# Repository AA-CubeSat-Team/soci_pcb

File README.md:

# soci_pcb

## design_rules
Directory for the design rules of various PCB manufacturers.

## libraries
Directory for Eagle part/component libraries used across PCB designs.

## projects
Repository for PCBs designed for soci in EAGLE

Make sure to update your libraries, design rules, and projects paths by going to Options -> Directories in EAGLE.

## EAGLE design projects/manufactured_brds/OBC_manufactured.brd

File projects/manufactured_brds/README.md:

## This folder Contains all of the Eagle files for boards that have been previously manufactured

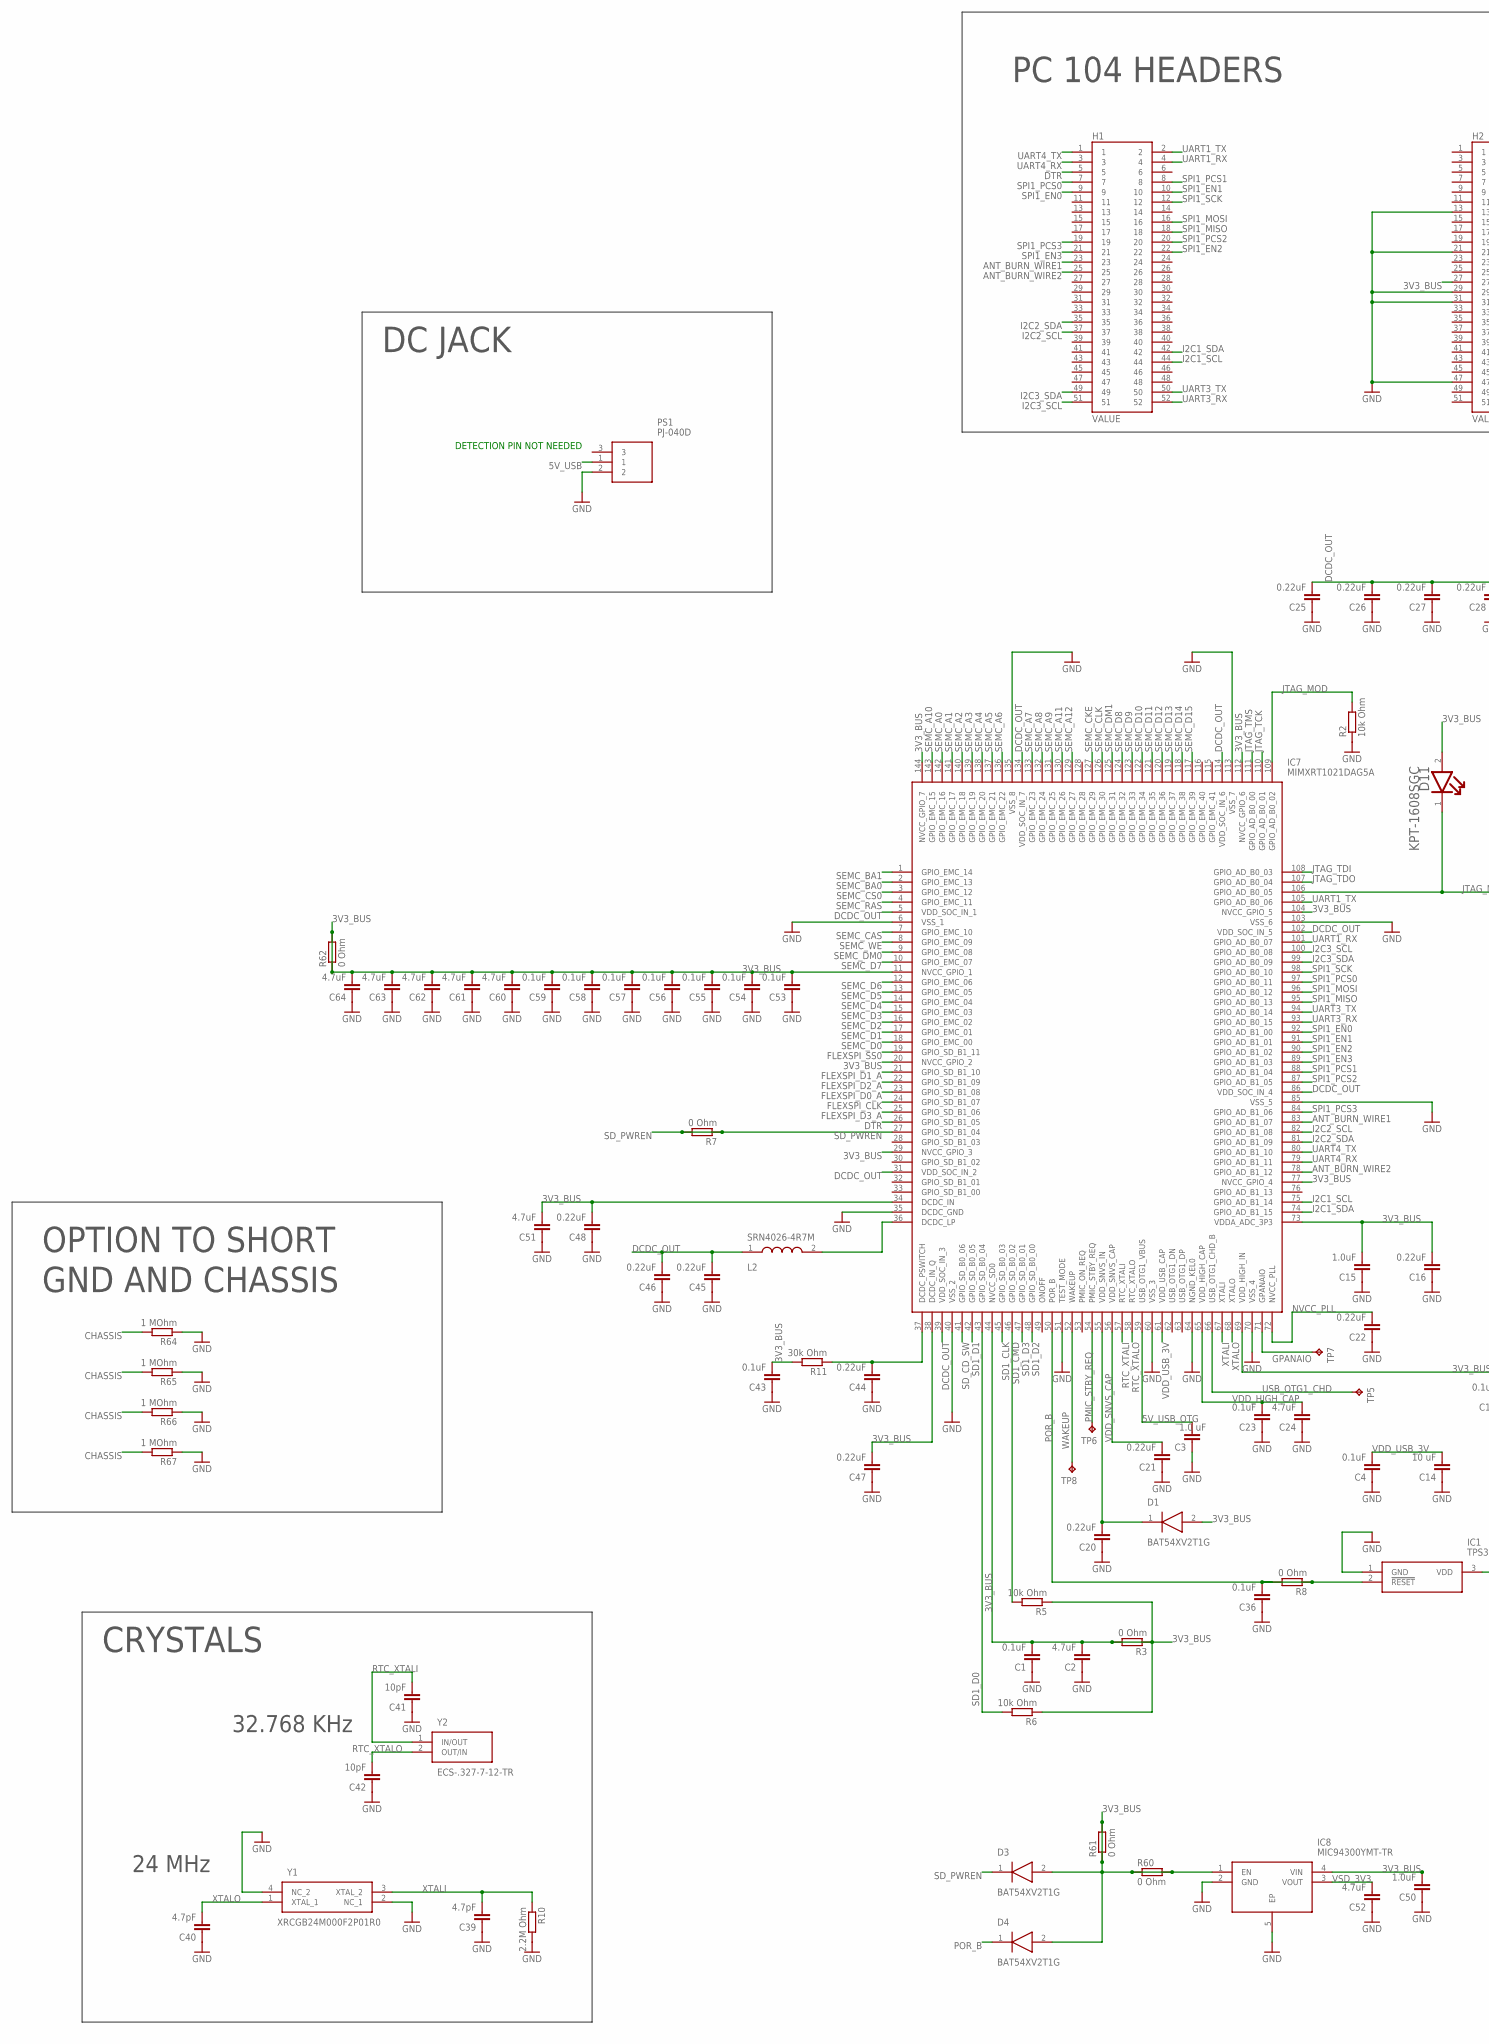
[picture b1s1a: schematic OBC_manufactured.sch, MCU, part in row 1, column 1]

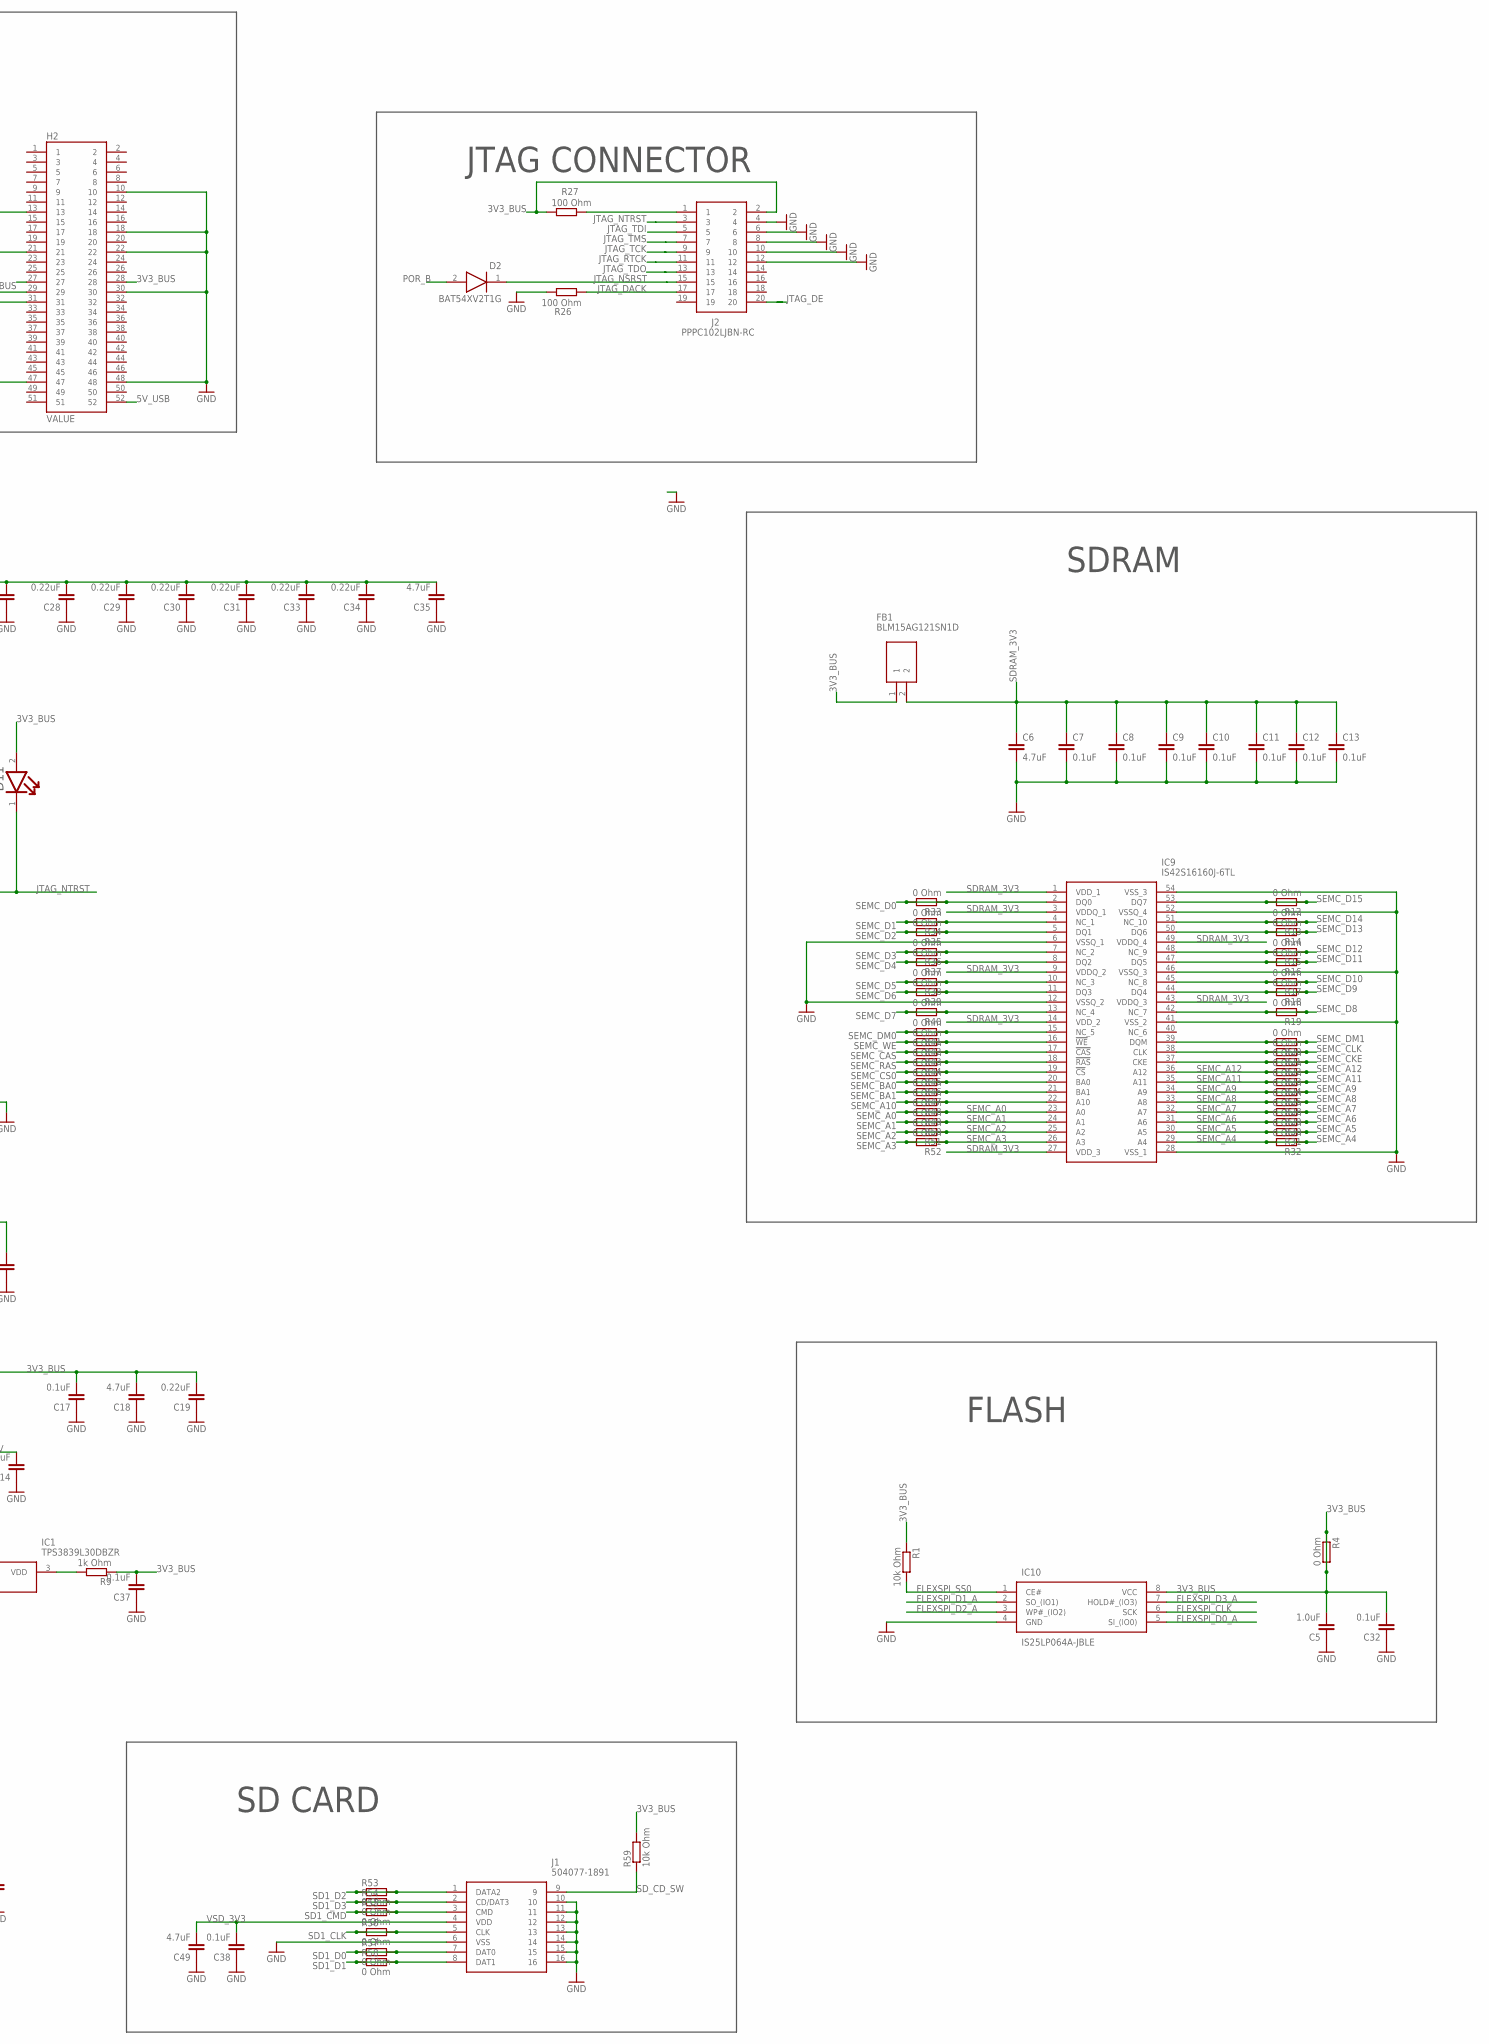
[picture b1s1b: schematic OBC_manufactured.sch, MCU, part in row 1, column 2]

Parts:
C1, C4, C7, C8, C9, C10, C11, C12, C13, C17, C23, C32, C36, C37, C38, C43, C53, C54, C55, C56, C57, C58, C59: 0.1uF; C0402K
C2, C6, C18, C24, C35, C49, C51, C52, C60, C61, C62, C63, C64: 4.7uF; C0402K
C3: 1.0 uF; C0402K
C5, C15, C50: 1.0uF; C0402K
C14: 10 uF; C0402K
C16, C19, C20, C21, C22, C25, C26, C27, C28, C29, C30, C31, C33, C34, C44, C45, C46, C47, C48: 0.22uF; C0402K
C39, C40: 4.7pF; C0402K
C41, C42: 10pF; C0402K
D1, D2, D3, D4: BAT54XV2T1G; SODFL1608X70N
D11: KINGBRIGHT_KPT-1608SGCKINGBRIGHT_KPT-1608SGC_0_0; KINGBRIGHT_KPT-1608SGC_0
FB1: BLM15AG121SN1D; NFZ15SG152SN10B
H1, H2: ESQ-126-39-G-D; SAMTEC_ESQ-126-39-G-D
IC1: TPS3839L30DBZR; SOT95P237X112-3N
IC7: MIMXRT1021DAG5A; QFP50P2200X2200X160-144N
IC8: MIC94300YMT-TR; SON50P160X120X60-5N
IC9: IS42S16160J-6TL; SOP80P1176X120-54N
IC10: IS25LP064A-JBLE; SOIC127P790X216-8N
J1: 504077-1891; 5040771891
J2: PPPC102LJBN-RC; RHDRRA20W60P254X254_2X10_2590X
L2: SRN4026-4R7M; SRN4026
PS1: PJ-040D; PJ040D
R1, R2, R5, R6, R59: 10k Ohm; R0402
R3, R4, R7, R8, R12, R13, R14, R15, R16, R17, R18, R19, R20, R21, R22, R23, R24, R25, R28, R29, R30, R31, R32, R33, R34, R35, R36, R37, R38, R39, R40, R41, R42, R43, R44, R45, R46, R47, R48, R49, R50, R51, R52, R53, R54, R55, R56, R57, R58, R60, R61, R62: 0 Ohm; R0402
R9: 1k Ohm; R0402
R10: 2.2M Ohm; R0402
R11: 30k Ohm; R0402
R26, R27: 100 Ohm; R0402
R64, R65, R66, R67: 1 MOhm; R0805
TP5, TP6, TP7, TP8: TPTP06R; TP06R
Y1: XRCGB24M000F2P01R0
Y2: ECS-.327-7-12-TR; ECS327712TR

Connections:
3V3_BUS: C1.2, C2.2, C5.2, C15.2, C16.2, C17.2, C18.2, C19.2, C32.2, C37.2, C43.2, C47.2, C48.2, C50.2, C51.2, C53.2, C54.2, C55.2, C56.2, C57.2, C58.2, C59.2, C60.2, C61.2, C62.2, C63.2, C64.2, D1.2 (A), D3.2 (A), D4.2 (A), D11.2 (ANODE), FB1.1, H2.27, H2.28, IC7.11 (NVCC_GPIO_1), IC7.20 (NVCC_GPIO_2), IC7.29 (NVCC_GPIO_3), IC7.34 (DCDC_IN), IC7.38 (DCDC_IN_Q), IC7.44 (NVCC_SD0), IC7.69 (VDD_HIGH_IN), IC7.73 (VDDA_ADC_3P3), IC7.77 (NVCC_GPIO_4), IC7.104 (NVCC_GPIO_5), IC7.112 (NVCC_GPIO_6), IC7.144 (NVCC_GPIO_7), IC8.1 (EN), IC8.4 (VIN), IC10.8 (VCC), J2.2, R1.1, R3.1, R3.2, R4.1, R4.2, R5.1, R6.1, R9.1, R11.2, R27.1, R59.2, R60.1, R60.2, R61.1, R61.2, R62.1, R62.2
5V_USB: H2.52, PS1.1
5V_USB_OTG: C3.2, IC7.59 (USB_OTG1_VBUS)
ANT_BURN_WIRE1: H1.23, IC7.83 (GPIO_AD_B1_07)
ANT_BURN_WIRE2: H1.25, IC7.78 (GPIO_AD_B1_12)
CHASSIS: R64.2, R65.2, R66.2, R67.2
DCDC_OUT: C25.2, C26.2, C27.2, C28.2, C29.2, C30.2, C31.2, C33.2, C34.2, C35.2, C45.2, C46.2, IC7.5 (VDD_SOC_IN_1), IC7.31 (VDD_SOC_IN_2), IC7.39 (VDD_SOC_IN_3), IC7.86 (VDD_SOC_IN_4), IC7.102 (VDD_SOC_IN_5), IC7.114 (VDD_SOC_IN_6), IC7.134 (VDD_SOC_IN_7), L2.1
DTR: H1.5, IC7.26 (GPIO_SD_B1_05)
FLEXSPI_CLK: IC7.24 (GPIO_SD_B1_07), IC10.6 (SCK)
FLEXSPI_D0_A: IC7.23 (GPIO_SD_B1_08), IC10.5 (SI_(IO0))
FLEXSPI_D1_A: IC7.21 (GPIO_SD_B1_10), IC10.2 (SO_(IO1))
FLEXSPI_D2_A: IC7.22 (GPIO_SD_B1_09), IC10.3 (WP#_(IO2))
FLEXSPI_D3_A: IC7.25 (GPIO_SD_B1_06), IC10.7 (HOLD#_(IO3))
FLEXSPI_SS0: IC7.19 (GPIO_SD_B1_11), IC10.1 (CE#), R1.2
GND: C1.1, C2.1, C3.1, C4.1, C5.1, C6.2, C7.2, C8.2, C9.2, C10.2, C11.2, C12.2, C13.2, C14.1, C15.1, C16.1, C17.1, C18.1, C19.1, C20.1, C21.1, C22.1, C23.1, C24.1, C25.1, C26.1, C27.1, C28.1, C29.1, C30.1, C31.1, C32.1, C33.1, C34.1, C35.1, C36.1, C37.1, C38.1, C39.1, C40.1, C41.1, C42.1, C43.1, C44.1, C45.1, C46.1, C47.1, C48.1, C49.1, C50.1, C51.1, C52.1, C53.1, C54.1, C55.1, C56.1, C57.1, C58.1, C59.1, C60.1, C61.1, C62.1, C63.1, C64.1, H2.10, H2.13, H2.18, H2.21, H2.22, H2.29, H2.30, H2.31, H2.47, H2.48, IC1.1 (GND), IC7.6 (VSS_1), IC7.35 (DCDC_GND), IC7.40 (VSS_2), IC7.51 (TEST_MODE), IC7.60 (VSS_3), IC7.64 (NGND_KEL0), IC7.70 (VSS_4), IC7.85 (VSS_5), IC7.103 (VSS_6), IC7.113 (VSS_7), IC7.135 (VSS_8), IC8.2 (GND), IC8.5 (EP), IC9.6 (VSSQ_1), IC9.12 (VSSQ_2), IC9.28 (VSS_1), IC9.41 (VSS_2), IC9.46 (VSSQ_3), IC9.52 (VSSQ_4), IC9.54 (VSS_3), IC10.4 (GND), J1.6 (VSS), J1.10, J1.11, J1.12, J1.13, J1.14, J1.15, J1.16, J2.4, J2.6, J2.8, J2.10, J2.12, PS1.2, R2.1, R10.2, R26.2, R64.1, R65.1, R66.1, R67.1, Y1.2 (NC_1), Y1.4 (NC_2)
GPANAIO: IC7.71 (GPANAIO), TP7.TP
I2C1_SCL: H1.44, IC7.75 (GPIO_AD_B1_14)
I2C1_SDA: H1.42, IC7.74 (GPIO_AD_B1_15)
I2C2_SCL: H1.37, IC7.82 (GPIO_AD_B1_08)
I2C2_SDA: H1.35, IC7.81 (GPIO_AD_B1_09)
I2C3_SCL: H1.51, IC7.100 (GPIO_AD_B0_08)
I2C3_SDA: H1.49, IC7.99 (GPIO_AD_B0_09)
JTAG_DACK: J2.17, R26.1
JTAG_DE: J2.20
JTAG_MOD: IC7.109 (GPIO_AD_B0_02), R2.2
JTAG_NSRST: D2.1 (K), J2.15
JTAG_NTRST: D11.1 (CATHODE), IC7.106 (GPIO_AD_B0_05), J2.3
JTAG_RTCK: J2.11
JTAG_TCK: IC7.110 (GPIO_AD_B0_01), J2.9
JTAG_TDI: IC7.108 (GPIO_AD_B0_03), J2.5
JTAG_TDO: IC7.107 (GPIO_AD_B0_04), J2.13
JTAG_TMS: IC7.111 (GPIO_AD_B0_00), J2.7
unnamed: J2.1, R27.2
unnamed: IC1.3 (VDD), R9.2
unnamed: IC7.36 (DCDC_LP), L2.2
unnamed: C44.2, IC7.37 (DCDC_PSWITCH), R11.1
unnamed: C20.2, D1.1 (K), IC7.55 (VDD_SNVS_IN)
NVCC_PLL: C22.2, IC7.72 (NVCC_PLL)
PMIC_STBY_REQ: IC7.54 (PMIC_STBY_REQ), TP6.TP
POR_B: C36.2, D2.2 (A), D4.1 (K), IC1.2 (!RESET), IC7.50 (POR_B), R8.1, R8.2
RTC_XTALI: C41.2, IC7.57 (RTC_XTALI), Y2.1 (IN/OUT)
RTC_XTALO: C42.2, IC7.58 (RTC_XTALO), Y2.2 (OUT/IN)
SD1_CLK: IC7.45 (GPIO_SD_B0_03), J1.5 (CLK), R56.1, R56.2
SD1_CMD: IC7.46 (GPIO_SD_B0_02), J1.3 (CMD), R5.2, R55.1, R55.2
SD1_D0: IC7.43 (GPIO_SD_B0_04), J1.7 (DAT0), R6.2, R57.1, R57.2
SD1_D1: IC7.42 (GPIO_SD_B0_05), J1.8 (DAT1), R58.1, R58.2
SD1_D2: IC7.48 (GPIO_SD_B0_00), J1.1 (DATA2), R53.1, R53.2
SD1_D3: IC7.47 (GPIO_SD_B0_01), J1.2 (CD/DAT3), R54.1, R54.2
SDRAM_3V3: C6.1, C7.1, C8.1, C9.1, C10.1, C11.1, C12.1, C13.1, FB1.2, IC9.1 (VDD_1), IC9.3 (VDDQ_1), IC9.9 (VDDQ_2), IC9.14 (VDD_2), IC9.27 (VDD_3), IC9.43 (VDDQ_3), IC9.49 (VDDQ_4)
SD_CD_SW: IC7.41 (GPIO_SD_B0_06), J1.9, R59.1
SD_PWREN: D3.1 (K), IC7.27 (GPIO_SD_B1_04), R7.1, R7.2
SEMC_A0: IC7.142 (GPIO_EMC_16), IC9.23 (A0), R49.1, R49.2
SEMC_A1: IC7.141 (GPIO_EMC_17), IC9.24 (A1), R50.1, R50.2
SEMC_A2: IC7.140 (GPIO_EMC_18), IC9.25 (A2), R51.1, R51.2
SEMC_A3: IC7.139 (GPIO_EMC_19), IC9.26 (A3), R52.1, R52.2
SEMC_A4: IC7.138 (GPIO_EMC_20), IC9.29 (A4), R32.1, R32.2
SEMC_A5: IC7.137 (GPIO_EMC_21), IC9.30 (A5), R31.1, R31.2
SEMC_A6: IC7.136 (GPIO_EMC_22), IC9.31 (A6), R30.1, R30.2
SEMC_A7: IC7.133 (GPIO_EMC_23), IC9.32 (A7), R29.1, R29.2
SEMC_A8: IC7.132 (GPIO_EMC_24), IC9.33 (A8), R28.1, R28.2
SEMC_A9: IC7.131 (GPIO_EMC_25), IC9.34 (A9), R25.1, R25.2
SEMC_A10: IC7.143 (GPIO_EMC_15), IC9.22 (A10), R48.1, R48.2
SEMC_A11: IC7.130 (GPIO_EMC_26), IC9.35 (A11), R24.1, R24.2
SEMC_A12: IC7.129 (GPIO_EMC_27), IC9.36 (A12), R23.1, R23.2
SEMC_BA0: IC7.2 (GPIO_EMC_13), IC9.20 (BA0), R46.1, R46.2
SEMC_BA1: IC7.1 (GPIO_EMC_14), IC9.21 (BA1), R47.1, R47.2
SEMC_CAS: IC7.7 (GPIO_EMC_10), IC9.17 (!CAS), R43.1, R43.2
SEMC_CKE: IC7.127 (GPIO_EMC_29), IC9.37 (CKE), R22.1, R22.2
SEMC_CLK: IC7.126 (GPIO_EMC_30), IC9.38 (CLK), R21.1, R21.2
SEMC_CS0: IC7.3 (GPIO_EMC_12), IC9.19 (!CS), R45.1, R45.2
SEMC_D0: IC7.18 (GPIO_EMC_00), IC9.2 (DQ0), R33.1, R33.2
SEMC_D1: IC7.17 (GPIO_EMC_01), IC9.4 (NC_1), R34.1, R34.2
SEMC_D2: IC7.16 (GPIO_EMC_02), IC9.5 (DQ1), R35.1, R35.2
SEMC_D3: IC7.15 (GPIO_EMC_03), IC9.7 (NC_2), R36.1, R36.2
SEMC_D4: IC7.14 (GPIO_EMC_04), IC9.8 (DQ2), R37.1, R37.2
SEMC_D5: IC7.13 (GPIO_EMC_05), IC9.10 (NC_3), R38.1, R38.2
SEMC_D6: IC7.12 (GPIO_EMC_06), IC9.11 (DQ3), R39.1, R39.2
SEMC_D7: IC7.10 (GPIO_EMC_07), IC9.13 (NC_4), R40.1, R40.2
SEMC_D8: IC7.124 (GPIO_EMC_32), IC9.42 (NC_7), R19.1, R19.2
SEMC_D9: IC7.123 (GPIO_EMC_33), IC9.44 (DQ4), R18.1, R18.2
SEMC_D10: IC7.122 (GPIO_EMC_34), IC9.45 (NC_8), R17.1, R17.2
SEMC_D11: IC7.121 (GPIO_EMC_35), IC9.47 (DQ5), R16.1, R16.2
SEMC_D12: IC7.120 (GPIO_EMC_36), IC9.48 (NC_9), R15.1, R15.2
SEMC_D13: IC7.119 (GPIO_EMC_37), IC9.50 (DQ6), R14.1, R14.2
SEMC_D14: IC7.118 (GPIO_EMC_38), IC9.51 (NC_10), R13.1, R13.2
SEMC_D15: IC7.117 (GPIO_EMC_39), IC9.53 (DQ7), R12.1, R12.2
SEMC_DM0: IC7.9 (GPIO_EMC_08), IC9.15 (NC_5), R41.1, R41.2
SEMC_DM1: IC7.125 (GPIO_EMC_31), IC9.39 (DQM), R20.1, R20.2
SEMC_RAS: IC7.4 (GPIO_EMC_11), IC9.18 (!RAS), R44.1, R44.2
SEMC_WE: IC7.8 (GPIO_EMC_09), IC9.16 (!WE), R42.1, R42.2
SPI1_EN0: H1.9, IC7.92 (GPIO_AD_B1_00)
SPI1_EN1: H1.10, IC7.91 (GPIO_AD_B1_01)
SPI1_EN2: H1.22, IC7.90 (GPIO_AD_B1_02)
SPI1_EN3: H1.21, IC7.89 (GPIO_AD_B1_03)
SPI1_MISO: H1.18, IC7.95 (GPIO_AD_B0_13)
SPI1_MOSI: H1.16, IC7.96 (GPIO_AD_B0_12)
SPI1_PCS0: H1.7, IC7.97 (GPIO_AD_B0_11)
SPI1_PCS1: H1.8, IC7.88 (GPIO_AD_B1_04)
SPI1_PCS2: H1.20, IC7.87 (GPIO_AD_B1_05)
SPI1_PCS3: H1.19, IC7.84 (GPIO_AD_B1_06)
SPI1_SCK: H1.12, IC7.98 (GPIO_AD_B0_10)
UART1_RX: H1.4, IC7.101 (GPIO_AD_B0_07)
UART1_TX: H1.2, IC7.105 (GPIO_AD_B0_06)
UART3_RX: H1.52, IC7.93 (GPIO_AD_B0_15)
UART3_TX: H1.50, IC7.94 (GPIO_AD_B0_14)
UART4_RX: H1.3, IC7.79 (GPIO_AD_B1_11)
UART4_TX: H1.1, IC7.80 (GPIO_AD_B1_10)
USB_OTG1_CHD: IC7.66 (USB_OTG1_CHD_B), TP5.TP
VDD_HIGH_CAP: C23.2, C24.2, IC7.65 (VDD_HIGH_CAP)
VDD_SNVS_CAP: C21.2, IC7.56 (VDD_SNVS_CAP)
VDD_USB_3V: C4.2, C14.2, IC7.61 (VDD_USB_CAP)
VSD_3V3: C38.2, C49.2, C52.2, IC8.3 (VOUT), J1.4 (VDD)
WAKEUP: IC7.52 (WAKEUP), TP8.TP
XTALI: C39.2, IC7.67 (XTALI), R10.1, Y1.3 (XTAL_2)
XTALO: C40.2, IC7.68 (XTALO), Y1.1 (XTAL_1)

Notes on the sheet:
DETECTION PIN NOT NEEDED
DC JACK
PC 104 HEADERS
JTAG CONNECTOR
SDRAM
FLASH
CRYSTALS
32.768 KHz
24 MHz
SD CARD
OPTION TO SHORT
GND AND CHASSIS

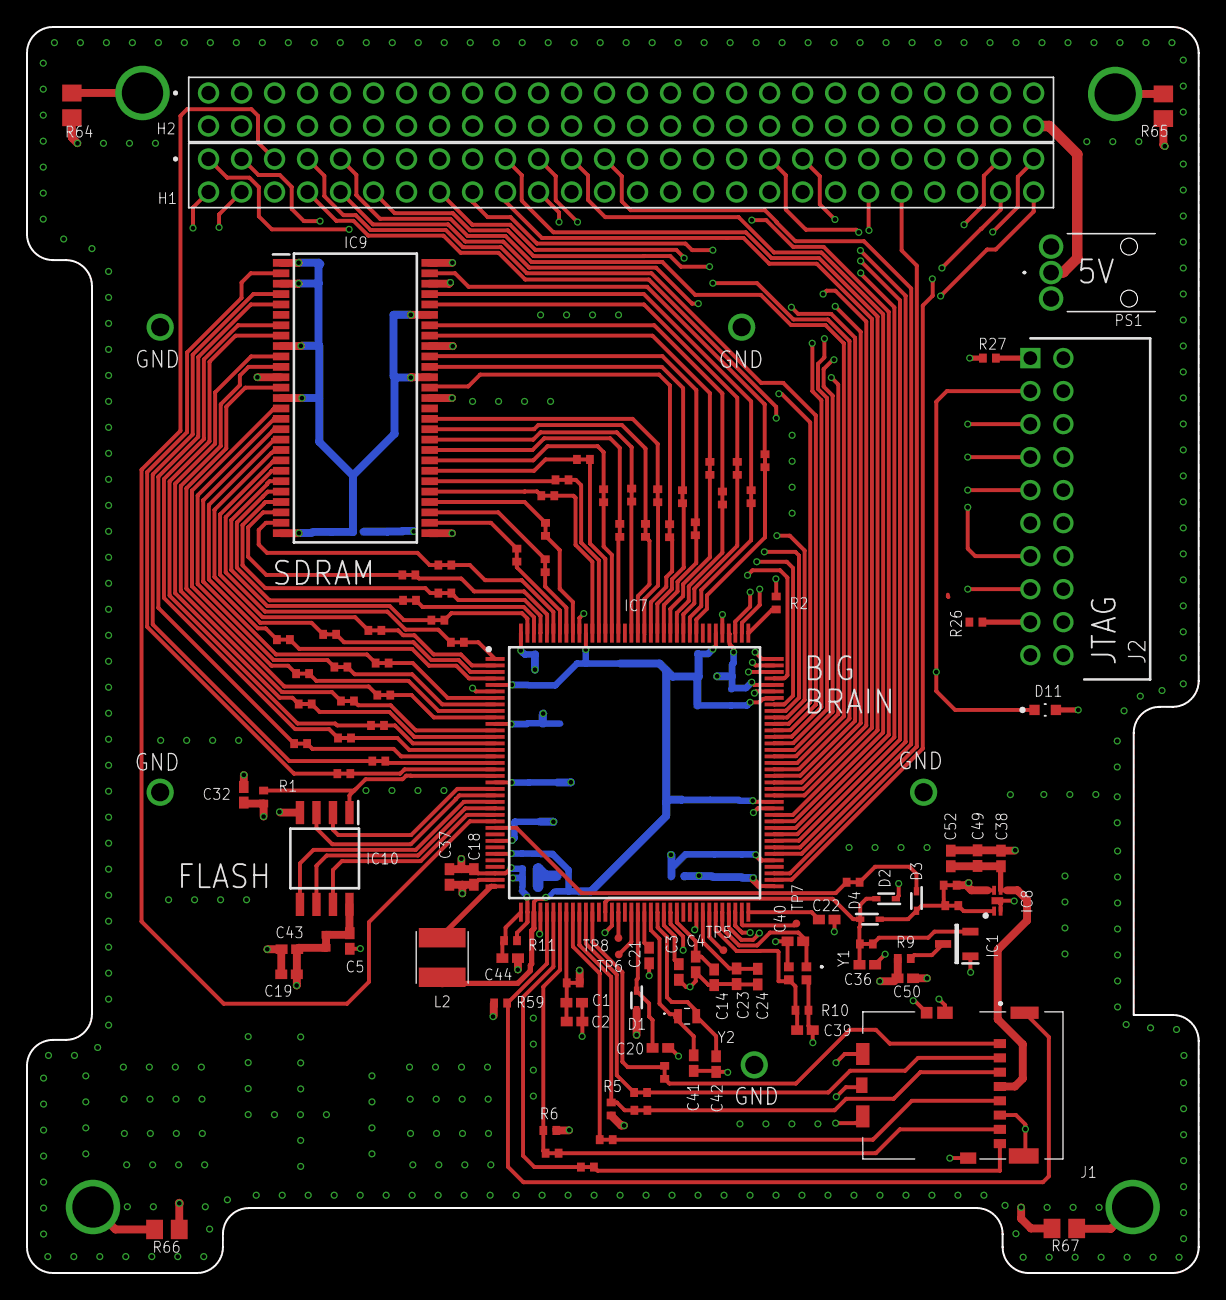
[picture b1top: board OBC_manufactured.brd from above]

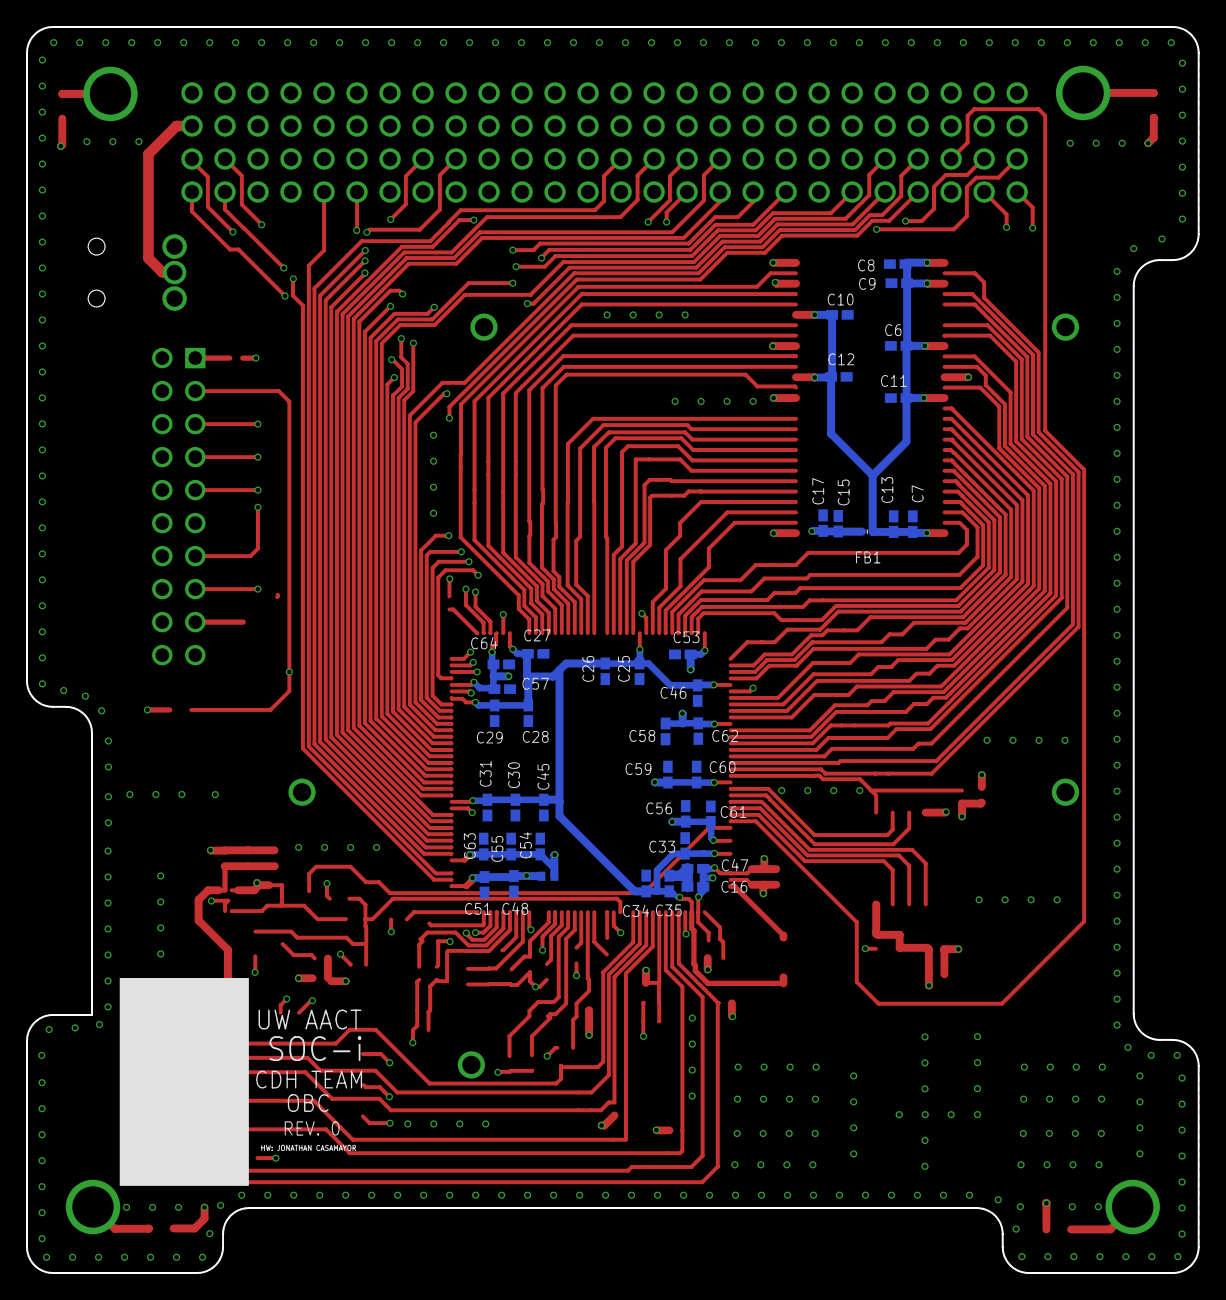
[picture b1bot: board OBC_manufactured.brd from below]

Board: 4 copper layers, 90.2 x 95.9 mm, 153 parts (40 on the bottom side), 113 nets.

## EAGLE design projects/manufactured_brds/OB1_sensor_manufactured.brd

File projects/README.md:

# CIA_board
Direcotry for CIA board EAGLE files.

# COM_R_board
Direcotry for COM_R board EAGLE files.

# eps_flatsat_module
Directory for the EPS module EAGLE files being designed for use in flatsat testing.

# onboard_flight_computer
Directory for the onboard flight computer EAGLE files.

# real_time_clock_testboard
Directory for the test board for the RTC circuit. The RTC was tested on a breadboard, and this board was never fabricated.

# sensor_board
Directory for the EAGLE files for the sensors board.

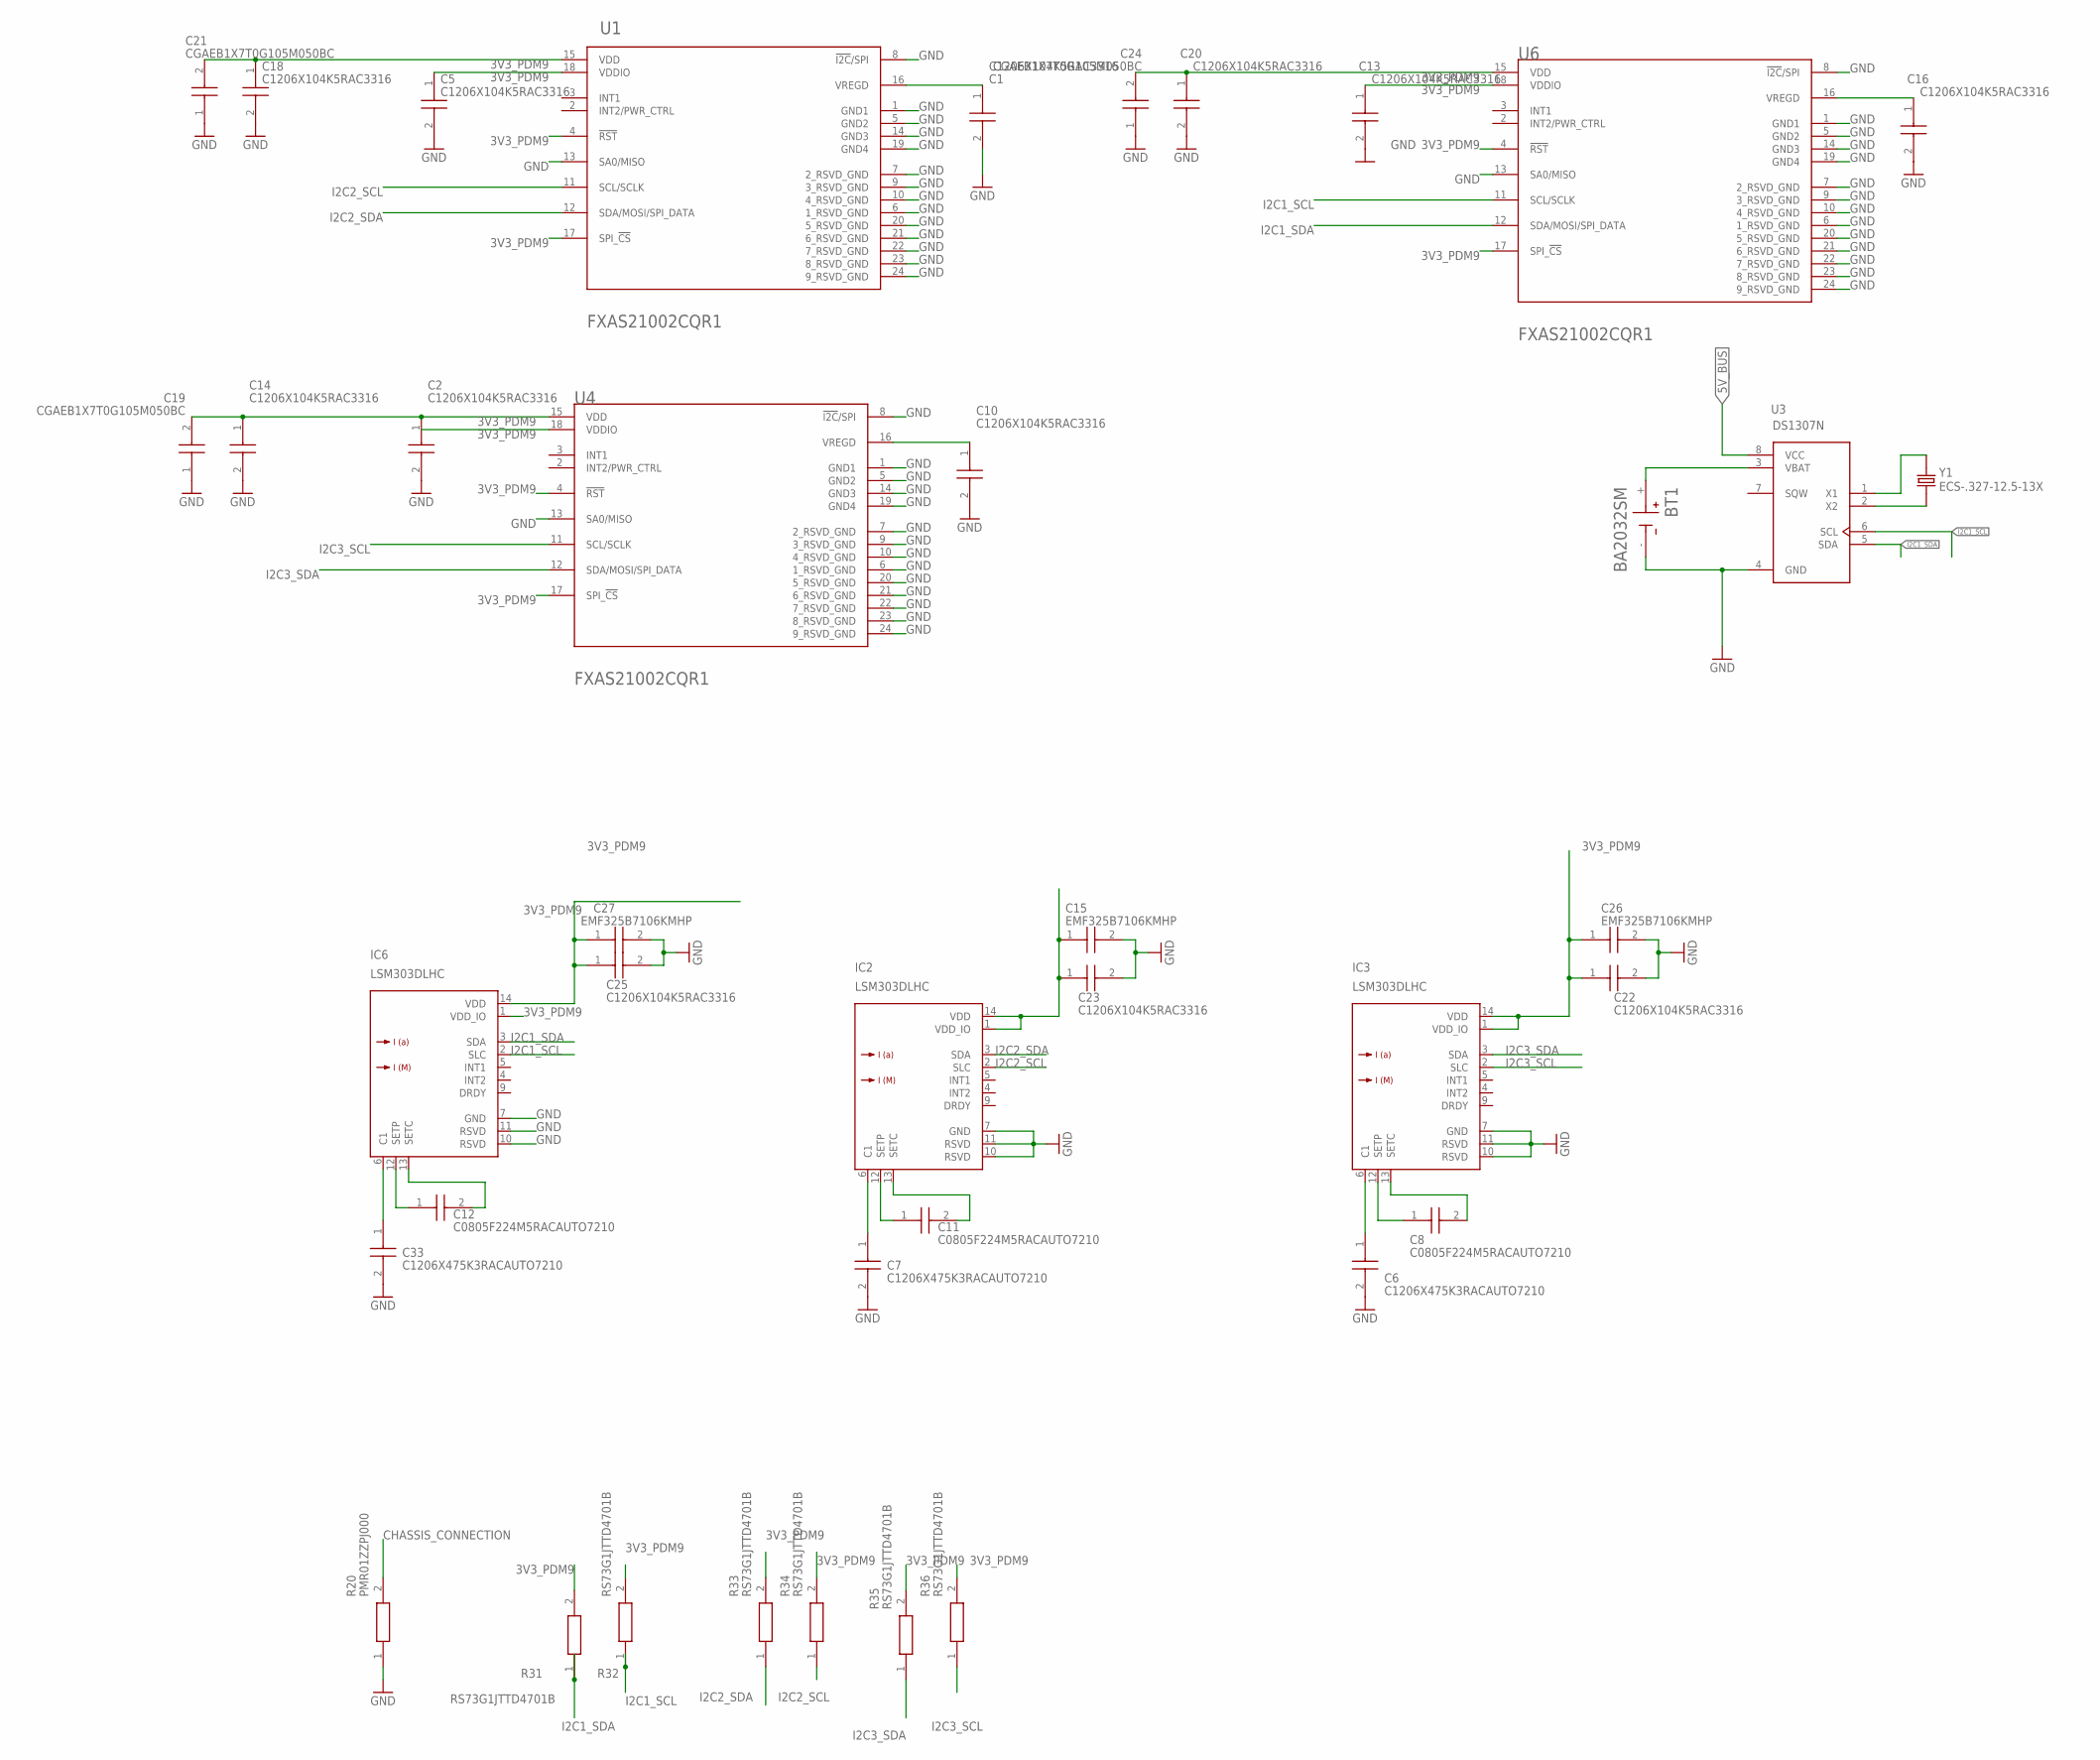
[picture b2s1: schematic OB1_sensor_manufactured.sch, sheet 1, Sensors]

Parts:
BT1: BA2032SM; BAT_BA2032SM
C1, C2, C5, C10, C13, C14, C16, C18, C20, C22, C23, C25: C1206X104K5RAC3316; CAPC3316X98N
C6, C7, C33: C1206X475K3RACAUTO7210; CAPC3316X195N
C8, C11, C12: C0805F224M5RACAUTO7210; CAPC2012X140N
C15, C26, C27: EMF325B7106KMHP; CAPC3225X270N
C19, C21, C24: CGAEB1X7T0G105M050BC; CAPC0611X68N
IC2, IC3, IC6: LSM303DLHC; LGA-14
R20: PMR01ZZPJ000; RESC1005X35N
R31, R32, R33, R34, R35, R36: RS73G1JTTD4701B; RESC1608X55N
U1, U4, U6: NXP_FXAS21002CQR1_EDITEDNXP_FXAS21002CQR1_0_0; NXP_FXAS21002CQR1_0_EDITED
U3: DS1307N; DIP762W47P254L991H457Q8
Y1: ECS-.327-12.5-13X; XTAL_ECS-.327-12.5-13X

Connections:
3V3_PDM9: C2.1, C5.1, C13.1, C14.1, C15.1, C18.1, C19.2, C20.1, C21.2, C22.1, C23.1, C24.2, C25.1, C26.1, C27.1, IC2.1 (VDD_IO), IC2.14 (VDD), IC3.1 (VDD_IO), IC3.14 (VDD), IC6.1 (VDD_IO), IC6.14 (VDD), R31.2, R32.2, R33.2, R34.2, R35.2, R36.2, U1.4 (!RST!), U1.15 (VDD), U1.17 (SPI_!CS!), U1.18 (VDDIO), U4.4 (!RST!), U4.15 (VDD), U4.17 (SPI_!CS!), U4.18 (VDDIO), U6.4 (!RST!), U6.15 (VDD), U6.17 (SPI_!CS!), U6.18 (VDDIO); also elsewhere on the board
5V_BUS: U3.8 (VCC); also elsewhere on the board
CHASSIS_CONNECTION: R20.2
GND: BT1.-, C1.2, C2.2, C5.2, C6.2, C7.2, C10.2, C13.2, C14.2, C15.2, C16.2, C18.2, C19.1, C20.2, C21.1, C22.2, C23.2, C24.1, C25.2, C26.2, C27.2, C33.2, IC2.7 (GND), IC2.10 (RSVD), IC2.11 (RSVD), IC3.7 (GND), IC3.10 (RSVD), IC3.11 (RSVD), IC6.7 (GND), IC6.10 (RSVD), IC6.11 (RSVD), R20.1, U1.1 (GND1), U1.5 (GND2), U1.6 (1_RSVD_GND), U1.7 (2_RSVD_GND), U1.8 (!I2C!/SPI), U1.9 (3_RSVD_GND), U1.10 (4_RSVD_GND), U1.13 (SA0/MISO), U1.14 (GND3), U1.19 (GND4), U1.20 (5_RSVD_GND), U1.21 (6_RSVD_GND), U1.22 (7_RSVD_GND), U1.23 (8_RSVD_GND), U1.24 (9_RSVD_GND), U3.4 (GND), U4.1 (GND1), U4.5 (GND2), U4.6 (1_RSVD_GND), U4.7 (2_RSVD_GND), U4.8 (!I2C!/SPI), U4.9 (3_RSVD_GND), U4.10 (4_RSVD_GND), U4.13 (SA0/MISO), U4.14 (GND3), U4.19 (GND4), U4.20 (5_RSVD_GND), U4.21 (6_RSVD_GND), U4.22 (7_RSVD_GND), U4.23 (8_RSVD_GND), U4.24 (9_RSVD_GND), U6.1 (GND1), U6.5 (GND2), U6.6 (1_RSVD_GND), U6.7 (2_RSVD_GND), U6.8 (!I2C!/SPI), U6.9 (3_RSVD_GND), U6.10 (4_RSVD_GND), U6.13 (SA0/MISO), U6.14 (GND3), U6.19 (GND4), U6.20 (5_RSVD_GND), U6.21 (6_RSVD_GND), U6.22 (7_RSVD_GND), U6.23 (8_RSVD_GND), U6.24 (9_RSVD_GND); also elsewhere on the board
I2C1_SCL: IC6.2 (SLC), R32.1, U3.6 (SCL), U6.11 (SCL/SCLK); also elsewhere on the board
I2C1_SDA: IC6.3 (SDA), R31.1, U3.5 (SDA), U6.12 (SDA/MOSI/SPI_DATA); also elsewhere on the board
I2C2_SCL: IC2.2 (SLC), R34.1, U1.11 (SCL/SCLK); also elsewhere on the board
I2C2_SDA: IC2.3 (SDA), R33.1, U1.12 (SDA/MOSI/SPI_DATA); also elsewhere on the board
I2C3_SCL: IC3.2 (SLC), R36.1, U4.11 (SCL/SCLK); also elsewhere on the board
I2C3_SDA: IC3.3 (SDA), R35.1, U4.12 (SDA/MOSI/SPI_DATA); also elsewhere on the board
unnamed: C6.1, IC3.6 (C1)
unnamed: C8.1, IC3.12 (SETP)
unnamed: C8.2, IC3.13 (SETC)
unnamed: C11.1, IC2.12 (SETP)
unnamed: C11.2, IC2.13 (SETC)
unnamed: C7.1, IC2.6 (C1)
unnamed: C12.1, IC6.12 (SETP)
unnamed: C12.2, IC6.13 (SETC)
unnamed: C33.1, IC6.6 (C1)
unnamed: U3.2 (X2), Y1.2
unnamed: U3.1 (X1), Y1.1
unnamed: BT1.+, U3.3 (VBAT)
unnamed: C10.1, U4.16 (VREGD)
unnamed: C1.1, U1.16 (VREGD)
unnamed: C16.1, U6.16 (VREGD)

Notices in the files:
parts and their libraries:
SparkFun-Boards: Licensing: Creative Commons ShareAlike 4.0 International - https://creativecommons.org/licenses/by-sa/4.0
